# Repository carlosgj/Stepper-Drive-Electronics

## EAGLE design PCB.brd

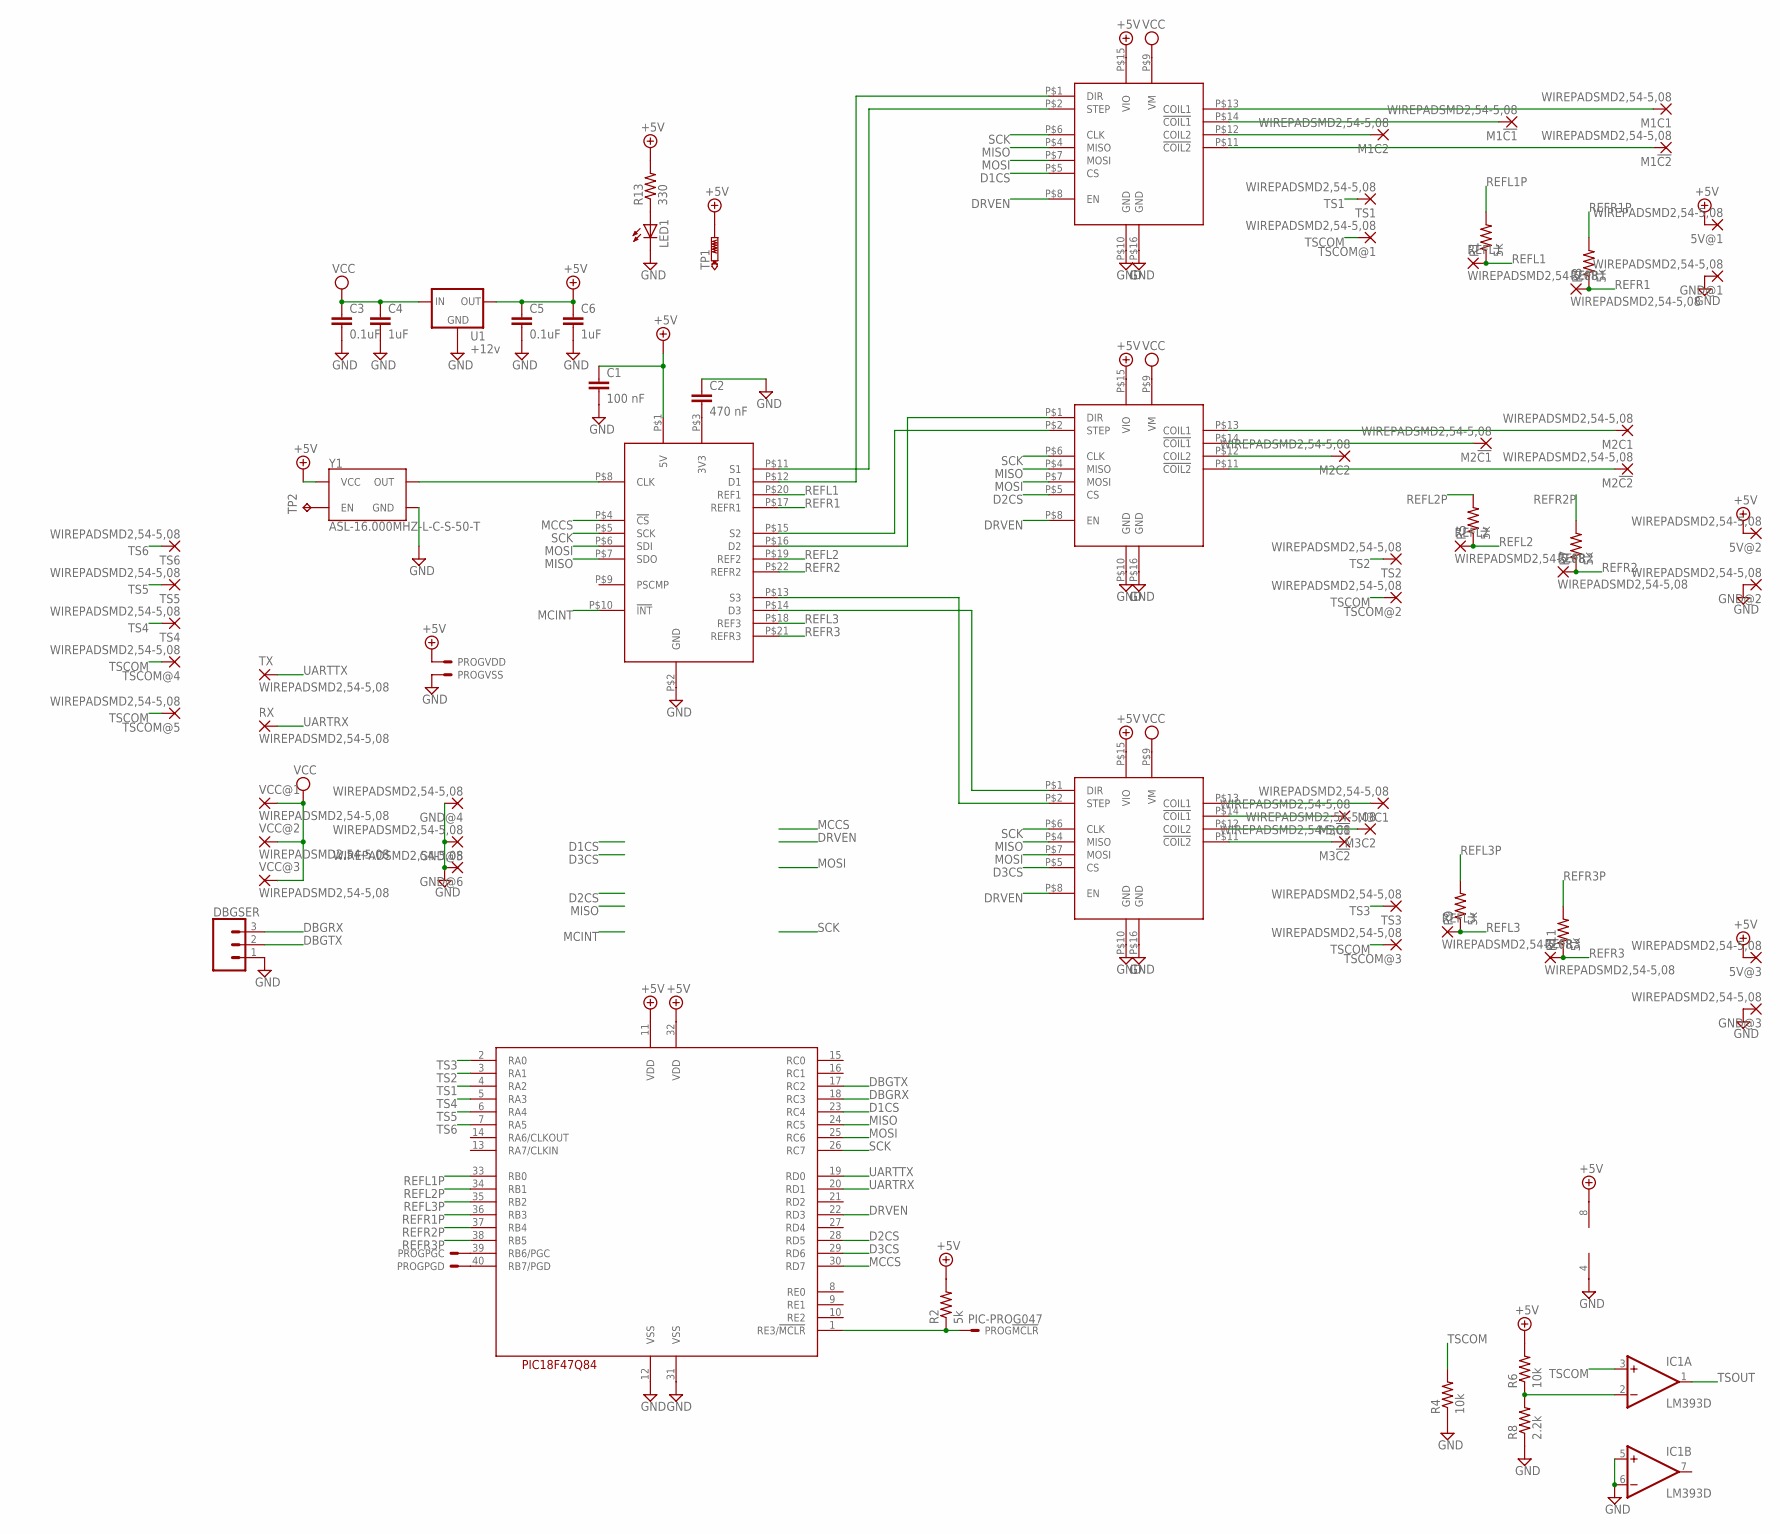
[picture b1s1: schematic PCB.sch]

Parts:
5V@1, 5V@2, 5V@3: WIREPADSMD2,54-5,08; SMD2,54-5,08
C1: 100 nF; C1206
C2: 470 nF; C1206
C3, C5: 0.1uF; C1206
C4, C6: 1uF; C1206
DBGSER: CONN_03; 1X03
DRV1, DRV2, DRV3: SILENTSTEPSTICK-DIPONLY
GND@1, GND@2, GND@3, GND@4, GND@5, GND@6: WIREPADSMD2,54-5,08; SMD2,54-5,08
IC1: LM393D; SO08
LED1: LEDCHIPLED_1206; CHIPLED_1206
M1!C1, M1!C2, M1C1, M1C2, M2!C1, M2!C2, M2C1, M2C2, M3!C1, M3!C2, M3C1, M3C2: WIREPADSMD2,54-5,08; SMD2,54-5,08
PROG: PIC-PROG047; 53047-05
R1, R2, R3, R5, R7, R9, R11: 5k; M1206
R4, R6: 10k; M1206
R8: 2.2k; M1206
R13: 330; M1206
REFL1, REFL2, REFL3: WIREPADSMD2,54-5,08; SMD2,54-5,08
REFR1, REFR2, REFR3: WIREPADSMD2,54-5,08; SMD2,54-5,08
RX: WIREPADSMD2,54-5,08; SMD2,54-5,08
TP1: PTR1PAD1-17; P1-17
TP2: TPB1,27; B1,27
TS1, TS2, TS3, TS4, TS5, TS6: WIREPADSMD2,54-5,08; SMD2,54-5,08
TSCOM@1, TSCOM@2, TSCOM@3, TSCOM@4, TSCOM@5: WIREPADSMD2,54-5,08; SMD2,54-5,08
TX: WIREPADSMD2,54-5,08; SMD2,54-5,08
U1: +12v; TO-252
U2: PIC18F47Q84; DIL40
U$1: TMC429-BOB
VCC@1, VCC@2, VCC@3: WIREPADSMD2,54-5,08; SMD2,54-5,08
Y1: ASL-16.000MHZ-L-C-S-50-T; OSCILLATOR-SMD-7X5-4PAD

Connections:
+5V: 5V@1.1, 5V@2.1, 5V@3.1, C1.1, C5.1, C6.1, DRV1.P$15 (VIO), DRV2.P$15 (VIO), DRV3.P$15 (VIO), IC1.8 (V+), PROG.2, R2.2, R6.2, R13.2, TP1.TP, U1.2 (OUT), U2.11 (VDD), U2.32 (VDD), U$1.P$1 (5V), Y1.4 (VCC)
D1CS: DRV1.P$5 (CS), U2.23 (RC4)
D2CS: DRV2.P$5 (CS), U2.28 (RD5)
D3CS: DRV3.P$5 (CS), U2.29 (RD6)
DBGRX: DBGSER.3, U2.18 (RC3)
DBGTX: DBGSER.2, U2.17 (RC2)
DRVEN: DRV1.P$8 (EN), DRV2.P$8 (EN), DRV3.P$8 (EN), U2.22 (RD3)
GND: C1.2, C2.1, C3.2, C4.2, C5.2, C6.2, DBGSER.1, DRV1.P$10 (GND), DRV1.P$16 (GND), DRV2.P$10 (GND), DRV2.P$16 (GND), DRV3.P$10 (GND), DRV3.P$16 (GND), GND@1.1, GND@2.1, GND@3.1, GND@4.1, GND@5.1, GND@6.1, IC1.4 (V-), IC1.5 (+IN), IC1.6 (-IN), LED1.C, PROG.3, R4.1, R8.1, U1.3 (GND), U2.12 (VSS), U2.31 (VSS), U$1.P$2 (GND), Y1.2 (GND)
MCCS: U2.30 (RD7), U$1.P$4 (!CS)
MCINT: U$1.P$10 (!INT)
MISO: DRV1.P$4 (MISO), DRV2.P$4 (MISO), DRV3.P$4 (MISO), U2.24 (RC5), U$1.P$7 (SDO)
MOSI: DRV1.P$7 (MOSI), DRV2.P$7 (MOSI), DRV3.P$7 (MOSI), U2.25 (RC6), U$1.P$6 (SDI)
unnamed: DRV1.P$1 (DIR), U$1.P$12 (D1)
unnamed: DRV1.P$2 (STEP), U$1.P$11 (S1)
unnamed: DRV2.P$2 (STEP), U$1.P$15 (S2)
unnamed: DRV2.P$1 (DIR), U$1.P$16 (D2)
unnamed: DRV3.P$2 (STEP), U$1.P$13 (S3)
unnamed: DRV3.P$1 (DIR), U$1.P$14 (D3)
unnamed: C2.2, U$1.P$3 (3V3)
unnamed: DRV1.P$13 (COIL1), M1C1.1
unnamed: DRV1.P$12 (COIL2), M1C2.1
unnamed: DRV1.P$14 (!COIL1), M1!C1.1
unnamed: DRV1.P$11 (!COIL2), M1!C2.1
unnamed: DRV2.P$14 (!COIL1), M2!C1.1
unnamed: DRV2.P$12 (COIL2), M2C2.1
unnamed: DRV2.P$11 (!COIL2), M2!C2.1
unnamed: DRV2.P$13 (COIL1), M2C1.1
unnamed: DRV3.P$14 (!COIL1), M3!C1.1
unnamed: DRV3.P$12 (COIL2), M3C2.1
unnamed: DRV3.P$13 (COIL1), M3C1.1
unnamed: DRV3.P$11 (!COIL2), M3!C2.1
unnamed: PROG.4, U2.40 (RB7/PGD)
unnamed: PROG.1, R2.1, U2.1 (RE3/!MCLR)
unnamed: PROG.5, U2.39 (RB6/PGC)
unnamed: U$1.P$8 (CLK), Y1.3 (OUT)
unnamed: TP2.TP, Y1.1 (EN)
unnamed: IC1.2 (-IN), R6.1, R8.2
unnamed: LED1.A, R13.1
REFL1: R1.1, REFL1.1, U$1.P$20 (REF1)
REFL1P: R1.2, U2.33 (RB0)
REFL2: R5.1, REFL2.1, U$1.P$19 (REF2)
REFL2P: R5.2, U2.34 (RB1)
REFL3: R9.1, REFL3.1, U$1.P$18 (REF3)
REFL3P: R9.2, U2.35 (RB2)
REFR1: R3.1, REFR1.1, U$1.P$17 (REFR1)
REFR1P: R3.2, U2.36 (RB3)
REFR2: R7.1, REFR2.1, U$1.P$22 (REFR2)
REFR2P: R7.2, U2.37 (RB4)
REFR3: R11.1, REFR3.1, U$1.P$21 (REFR3)
REFR3P: R11.2, U2.38 (RB5)
SCK: DRV1.P$6 (CLK), DRV2.P$6 (CLK), DRV3.P$6 (CLK), U2.26 (RC7), U$1.P$5 (SCK)
TS1: TS1.1, U2.4 (RA2)
TS2: TS2.1, U2.3 (RA1)
TS3: TS3.1, U2.2 (RA0)
TS4: TS4.1, U2.5 (RA3)
TS5: TS5.1, U2.6 (RA4)
TS6: TS6.1, U2.7 (RA5)
TSCOM: IC1.3 (+IN), R4.2, TSCOM@1.1, TSCOM@2.1, TSCOM@3.1, TSCOM@4.1, TSCOM@5.1
TSOUT: IC1.1 (OUT)
UARTRX: RX.1, U2.20 (RD1)
UARTTX: TX.1, U2.19 (RD0)
VCC: C3.1, C4.1, DRV1.P$9 (VM), DRV2.P$9 (VM), DRV3.P$9 (VM), U1.1 (IN), VCC@1.1, VCC@2.1, VCC@3.1

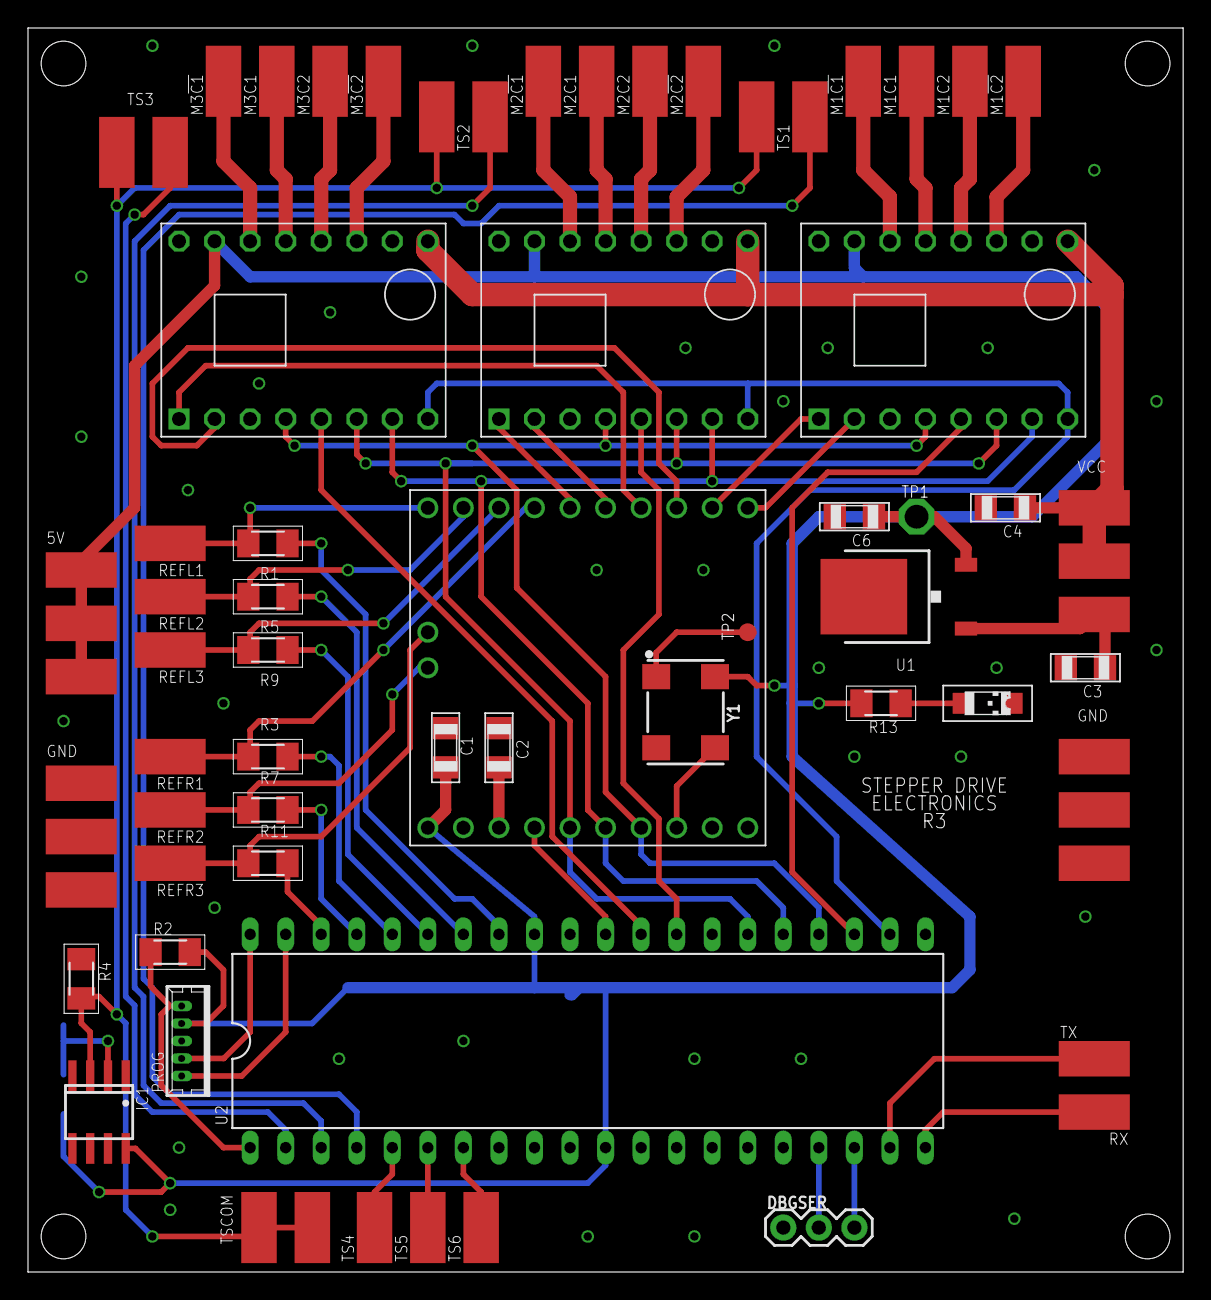
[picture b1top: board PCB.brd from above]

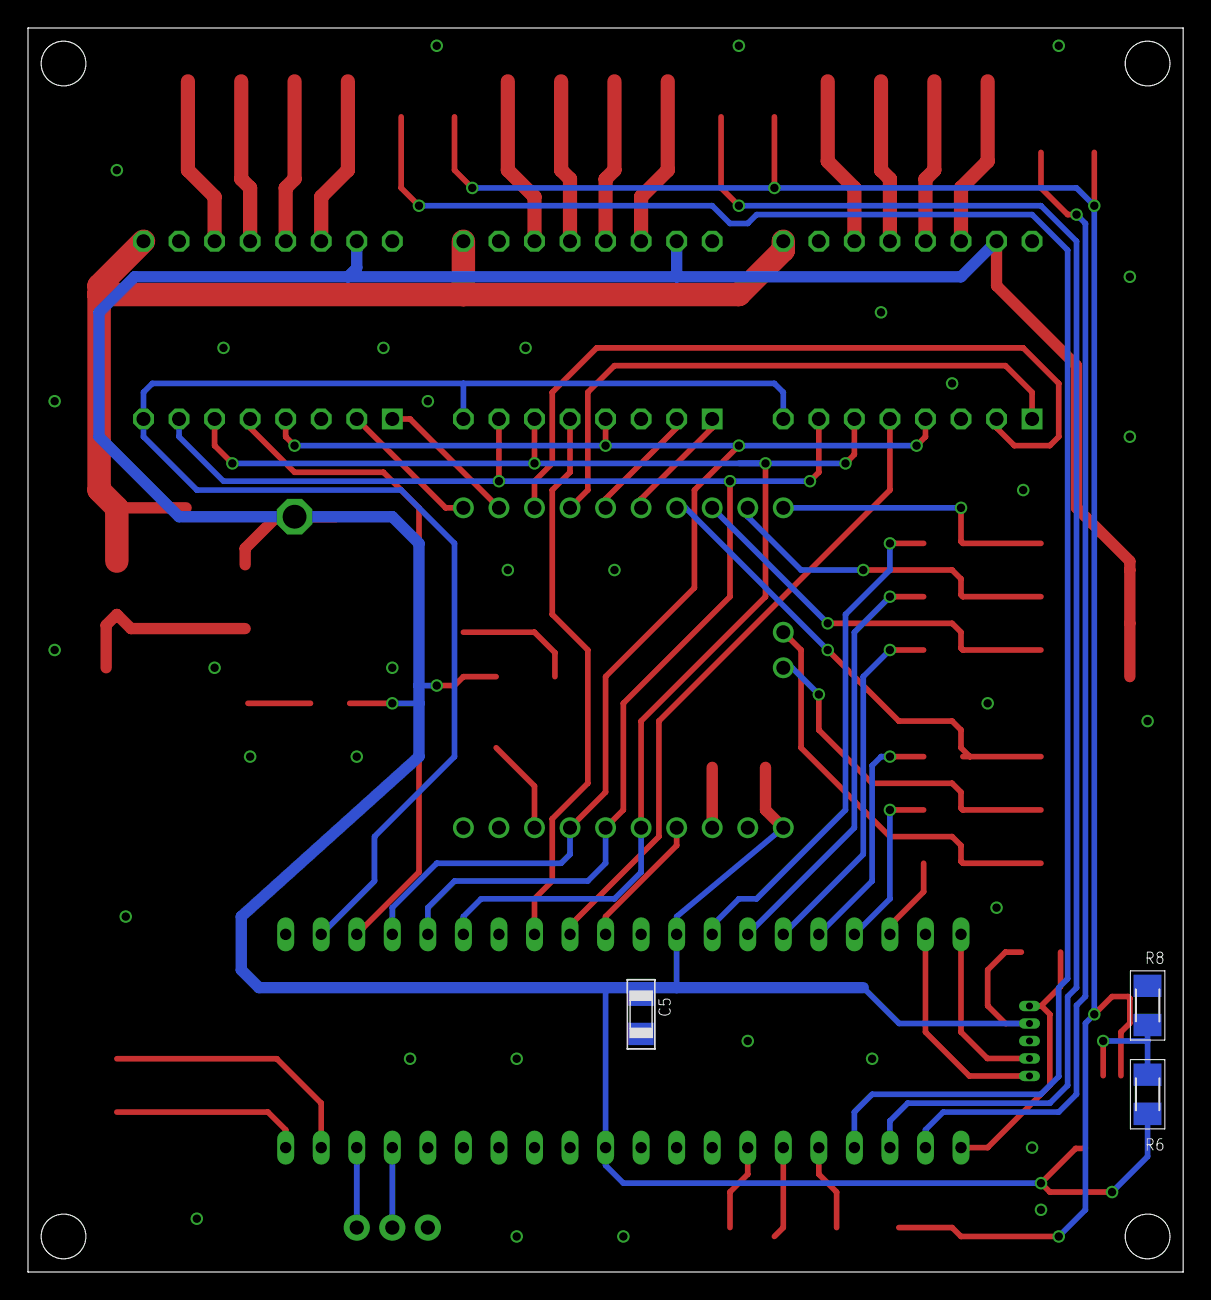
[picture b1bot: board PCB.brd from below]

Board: 2 copper layers, 82.5 x 88.9 mm, 73 parts (3 on the bottom side), 60 nets.

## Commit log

2021-01-18 HW Rev 1
2021-01-18 Switching to make D9 for power input
2021-01-31 Adding 5V TP
2021-01-31 Initial code
2021-01-31 gitignore
2021-01-31 Code work
2021-01-31 Adding PIC test point
2021-01-31 Improving TMC2130 silkscreen
2021-02-01 Tinkering
2021-02-07 Implementing SPI
2021-02-07 Working on Trinamic implementation
2021-02-07 CTDB work
2021-02-08 Working on serial implementation
2021-02-08 Actually return the received data
2021-02-08 Splitting boundary into start and stop bytes
2021-02-08 Trinamic skeletons
2021-02-09 Working on telemetry structure
2021-02-10 Work on Trinamic comms
2021-02-12 Adding voltage measurement
2021-02-12 Adding system voltage
2021-02-13 Setting SCK direction
2021-02-13 Adding error counter for unknown opcodes
2021-02-13 Implementing driver disable
2021-02-13 SPI seems to work
2021-02-15 Getting telemetry working
2021-02-15 COSMOS
2021-02-15 Comms debugging
2021-02-15 Improving default values
2021-02-16 Switching to big endian
2021-02-16 Working on TMC429 implementation
2021-02-16 Fixing a nasty buffer bug
2021-02-16 TMC429 basically works!
2021-02-16 Adding little endian sendBuf
2021-02-16 Working on TMC2130 implementation
2021-02-26 Basic motor driving works!
2021-02-26 Work on TMC2130 implementation
2021-03-04 Fixed a comms bug
2021-03-04 Oops
2021-03-04 Implemented homing
2021-03-07 Upgrading to 16F1847
2021-03-07 Real HW R1
2021-03-14 Updates to allow driving 2 motors
2021-03-18 Create LICENSE
2021-04-07 Cleanup
2021-04-07 Working on shadow registers
2022-08-11 Stuff
2023-01-17 Updating PCB design

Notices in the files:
parts and their libraries:
SparkFun-Clocks: Licensing: Creative Commons ShareAlike 4.0 International - https://creativecommons.org/licenses/by-sa/4.0
